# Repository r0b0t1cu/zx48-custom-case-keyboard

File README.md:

# ZX Spectrum 48k custom case, keyboard and keycaps

A custom 3D-printed case, keycap set, and keyboard PCB for the ZX Spectrum 48K.

## Why

This started with a ULA chip I had sitting around doing nothing, and a friend who handed me a [PABB Issue 3B PCB](https://www.pcbway.com/project/shareproject/ZX_Spectrum_48_Issue_3B_Redrawn.html). One thing led to another, and the mainboard needed a case and a keyboard to go with it — so I designed both from scratch, along with a few other addons along the way.

## Compatibility

The case is designed around the classic ZX Spectrum 48K PCB footprint and mounting hole layout. It's compatible with:

- Original ZX Spectrum 48K
- ZX Spectrum 48K+
- Any clone board sharing the same PCB size and mounting hole layout (confirmed working with the **Harlequin 128**)

The case is built to be tall enough to accomodate my mods. For example the [ZX Spectrum 27C512 EPROM Adapter](https://github.com/r0b0t1cu/ZX-Spectrum-27C512-EPROM-Adapter).

## What's included

### Case (`/case`)
A simplified, more angular take on the classic Spectrum enclosure, split into three printed parts: bottom shell, back plate, and top. A separate top variant is included for builds using a Harlequin 128 board.

The back plate is modeled to fit the [ZX-Spectrum-AV-Adapter](https://github.com/r0b0t1cu/ZX-Spectrum-AV-Adapter), not the stock Spectrum TV-out connector.

- `FREECAD/` — native FreeCAD source files
- `STEP/` — STEP exports
- `STL/` — ready-to-slice STL files

### Keycaps (`/keycaps`)
Full Spectrum 48K keycap set (letters, numbers, and CS/SS/SP/CR), modeled individually for two-color printing — each key has a separate body and legend (text) piece. Legends use the [Rubik](https://fonts.google.com/specimen/Rubik) typeface.

- `FREECAD/` — native FreeCAD source files, one per key
- `STEP/` — STEP exports
- `STL/` — one `-Body.stl` and one `-Text.stl` per key, for multi-material/multi-color printing
- `3MF/` — pre-arranged print-ready project files with color separation already set up (a Bambu Lab A1-specific version and a generic version)

### Keyboard PCB (`/keyboard-pcb`)
A custom keyboard PCB for use with Cherry MX (and compatible) switches.

Full KiCad project included, plus a fabrication-ready production folder (BOM, CPL, netlist, Gerbers) for ordering directly from a fab house such as PCBWay or JLCPCB.

---

If you enjoy my projects and would like to support my work, you can do so through PCBWay. You can also order the PCBs for this project directly from the link below. Every bit of support is appreciated!

<p>
  
</p>

---

## 3D Printing

- **Material:** PLA
- **Layer height:** 0.2 mm
- **Infill:** 15%
- **Orientation:** flat side down
- **Supports:** a few small supports needed

## Assembly

Case parts are held together with **M3 screws** — all mounting holes are sized for M3.

## Credits & licenses

- All files in this repository (case, keycaps, keyboard PCB) are released under the **MIT License** — see [LICENSE](LICENSE).
- Keycap legends use the **Rubik** typeface by Google Fonts, licensed under the [SIL Open Font License](https://fonts.google.com/specimen/Rubik).
- This case and keyboard are designed to fit a ZX Spectrum 48K mainboard such as [PABB's Issue 3B redraw](https://www.pcbway.com/project/shareproject/ZX_Spectrum_48_Issue_3B_Redrawn.html), which is a **separate project licensed CC BY-NC-SA** and is *not* included or redistributed here.

## Related projects

- [ZX-Spectrum-AV-Adapter](https://github.com/r0b0t1cu/ZX-Spectrum-AV-Adapter) — custom composite video mod
- [ZX-Spectrum-27C512-EPROM-Adapter](https://github.com/r0b0t1cu/ZX-Spectrum-27C512-EPROM-Adapter) — custom EPROM adapter

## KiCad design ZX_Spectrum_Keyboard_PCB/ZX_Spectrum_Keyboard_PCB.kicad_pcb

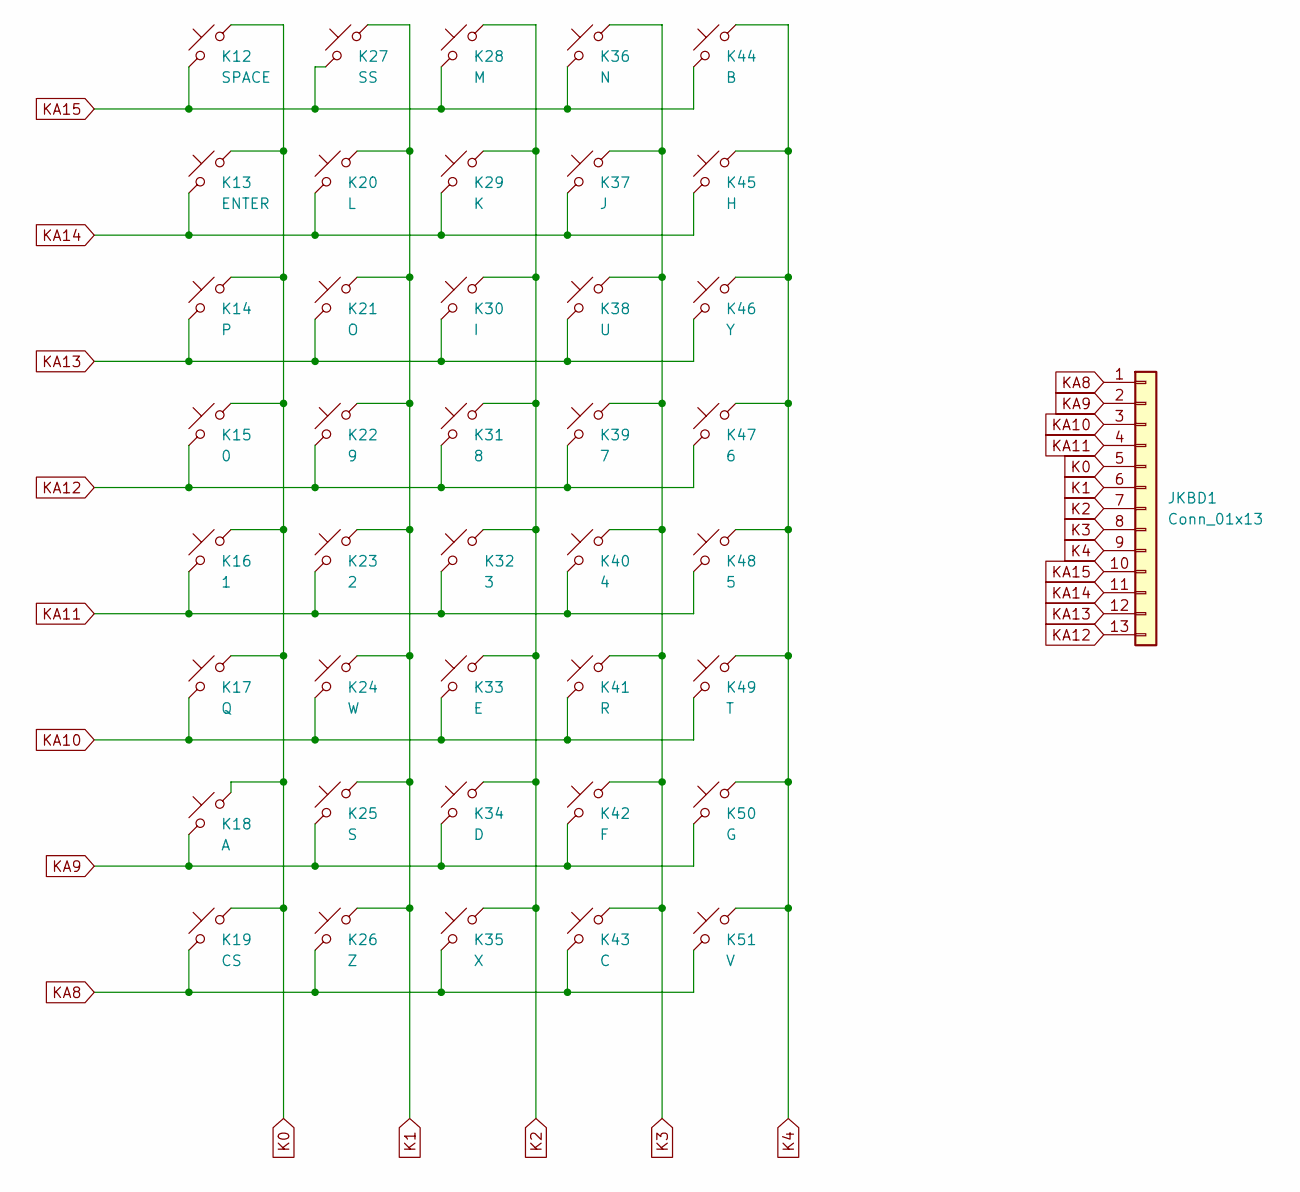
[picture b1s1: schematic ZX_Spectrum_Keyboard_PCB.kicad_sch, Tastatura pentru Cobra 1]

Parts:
JKBD1: Conn_01x13; PinSocket_1x13_P2.54mm_Vertical
K12: SPACE; SW_Cherry_MX_1.00u_PCB
K13: ENTER; SW_Cherry_MX_1.00u_PCB
K14: P; SW_Cherry_MX_1.00u_PCB
K15: 0; SW_Cherry_MX_1.00u_PCB
K16: 1; SW_Cherry_MX_1.00u_PCB
K17: Q; SW_Cherry_MX_1.00u_PCB
K18: A; SW_Cherry_MX_1.00u_PCB
K19: CS; SW_Cherry_MX_1.00u_PCB
K20: L; SW_Cherry_MX_1.00u_PCB
K21: O; SW_Cherry_MX_1.00u_PCB
K22: 9; SW_Cherry_MX_1.00u_PCB
K23: 2; SW_Cherry_MX_1.00u_PCB
K24: W; SW_Cherry_MX_1.00u_PCB
K25: S; SW_Cherry_MX_1.00u_PCB
K26: Z; SW_Cherry_MX_1.00u_PCB
K27: SS; SW_Cherry_MX_1.00u_PCB
K28: M; SW_Cherry_MX_1.00u_PCB
K29: K; SW_Cherry_MX_1.00u_PCB
K30: I; SW_Cherry_MX_1.00u_PCB
K31: 8; SW_Cherry_MX_1.00u_PCB
K32: 3; SW_Cherry_MX_1.00u_PCB
K33: E; SW_Cherry_MX_1.00u_PCB
K34: D; SW_Cherry_MX_1.00u_PCB
K35: X; SW_Cherry_MX_1.00u_PCB
K36: N; SW_Cherry_MX_1.00u_PCB
K37: J; SW_Cherry_MX_1.00u_PCB
K38: U; SW_Cherry_MX_1.00u_PCB
K39: 7; SW_Cherry_MX_1.00u_PCB
K40: 4; SW_Cherry_MX_1.00u_PCB
K41: R; SW_Cherry_MX_1.00u_PCB
K42: F; SW_Cherry_MX_1.00u_PCB
K43: C; SW_Cherry_MX_1.00u_PCB
K44: B; SW_Cherry_MX_1.00u_PCB
K45: H; SW_Cherry_MX_1.00u_PCB
K46: Y; SW_Cherry_MX_1.00u_PCB
K47: 6; SW_Cherry_MX_1.00u_PCB
K48: 5; SW_Cherry_MX_1.00u_PCB
K49: T; SW_Cherry_MX_1.00u_PCB
K50: G; SW_Cherry_MX_1.00u_PCB
K51: V; SW_Cherry_MX_1.00u_PCB

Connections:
K0: JKBD1.5, K12.2, K13.2, K14.2, K15.2, K16.2, K17.2, K18.2, K19.2
K1: JKBD1.6, K20.2, K21.2, K22.2, K23.2, K24.2, K25.2, K26.2, K27.2
K2: JKBD1.7, K28.2, K29.2, K30.2, K31.2, K32.2, K33.2, K34.2, K35.2
K3: JKBD1.8, K36.2, K37.2, K38.2, K39.2, K40.2, K41.2, K42.2, K43.2
K4: JKBD1.9, K44.2, K45.2, K46.2, K47.2, K48.2, K49.2, K50.2, K51.2
KA8: JKBD1.1, K19.1, K26.1, K35.1, K43.1, K51.1
KA9: JKBD1.2, K18.1, K25.1, K34.1, K42.1, K50.1
KA10: JKBD1.3, K17.1, K24.1, K33.1, K41.1, K49.1
KA11: JKBD1.4, K16.1, K23.1, K32.1, K40.1, K48.1
KA12: JKBD1.13, K15.1, K22.1, K31.1, K39.1, K47.1
KA13: JKBD1.12, K14.1, K21.1, K30.1, K38.1, K46.1
KA14: JKBD1.11, K13.1, K20.1, K29.1, K37.1, K45.1
KA15: JKBD1.10, K12.1, K27.1, K28.1, K36.1, K44.1

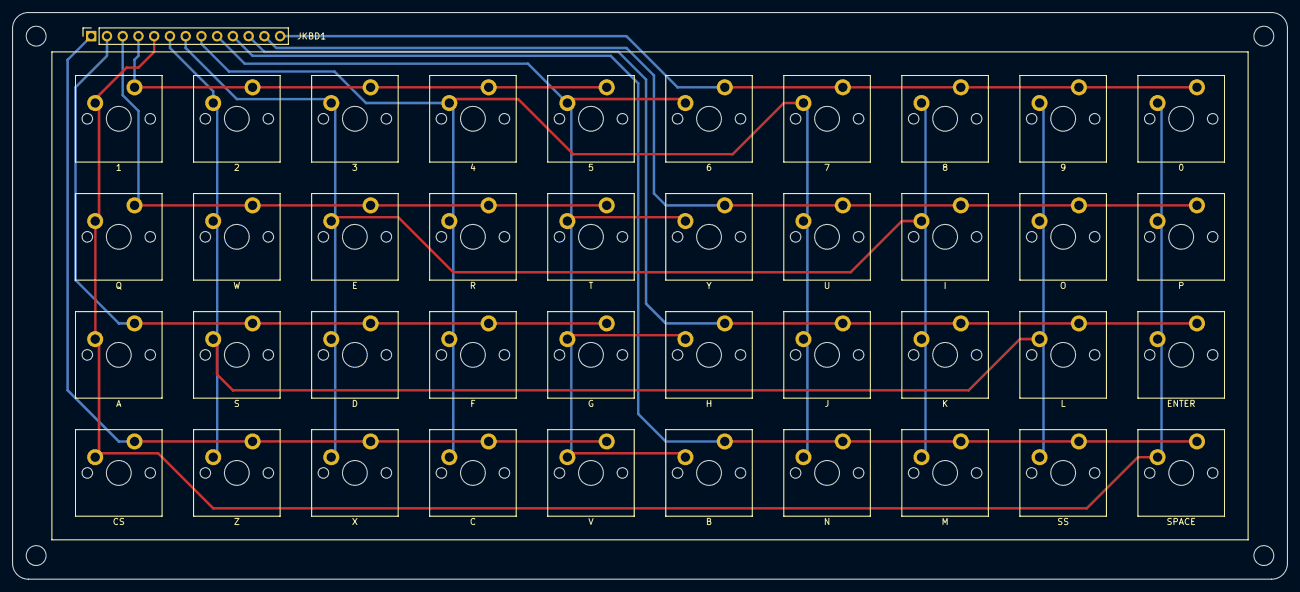
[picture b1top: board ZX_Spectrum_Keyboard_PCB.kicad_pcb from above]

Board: 2 copper layers, 205.7 x 91.4 mm, 45 parts (0 on the bottom side), 13 nets.

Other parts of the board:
M1, M2, M3, M4: MountingHole_3.2mm_M3

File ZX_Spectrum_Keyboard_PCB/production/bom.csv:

Designator,Footprint,Quantity,Value,LCSC Part #
JKBD1,PinSocket_1x13_P2.54mm_Vertical,1,Conn_01x13,
K12,SW_Cherry_MX_1.00u_PCB,1,SPACE,
K13,SW_Cherry_MX_1.00u_PCB,1,ENTER,
K14,SW_Cherry_MX_1.00u_PCB,1,P,
K15,SW_Cherry_MX_1.00u_PCB,1,0,
K16,SW_Cherry_MX_1.00u_PCB,1,1,
K17,SW_Cherry_MX_1.00u_PCB,1,Q,
K18,SW_Cherry_MX_1.00u_PCB,1,A,
K19,SW_Cherry_MX_1.00u_PCB,1,CS,
K20,SW_Cherry_MX_1.00u_PCB,1,L,
K21,SW_Cherry_MX_1.00u_PCB,1,O,
K22,SW_Cherry_MX_1.00u_PCB,1,9,
K23,SW_Cherry_MX_1.00u_PCB,1,2,
K24,SW_Cherry_MX_1.00u_PCB,1,W,
K25,SW_Cherry_MX_1.00u_PCB,1,S,
K26,SW_Cherry_MX_1.00u_PCB,1,Z,
K27,SW_Cherry_MX_1.00u_PCB,1,SS,
K28,SW_Cherry_MX_1.00u_PCB,1,M,
K29,SW_Cherry_MX_1.00u_PCB,1,K,
K30,SW_Cherry_MX_1.00u_PCB,1,I,
K31,SW_Cherry_MX_1.00u_PCB,1,8,
K32,SW_Cherry_MX_1.00u_PCB,1,3,
K33,SW_Cherry_MX_1.00u_PCB,1,E,
K34,SW_Cherry_MX_1.00u_PCB,1,D,
K35,SW_Cherry_MX_1.00u_PCB,1,X,
K36,SW_Cherry_MX_1.00u_PCB,1,N,
K37,SW_Cherry_MX_1.00u_PCB,1,J,
K38,SW_Cherry_MX_1.00u_PCB,1,U,
K39,SW_Cherry_MX_1.00u_PCB,1,7,
K40,SW_Cherry_MX_1.00u_PCB,1,4,
K41,SW_Cherry_MX_1.00u_PCB,1,R,
K42,SW_Cherry_MX_1.00u_PCB,1,F,
K43,SW_Cherry_MX_1.00u_PCB,1,C,
K44,SW_Cherry_MX_1.00u_PCB,1,B,
K45,SW_Cherry_MX_1.00u_PCB,1,H,
K46,SW_Cherry_MX_1.00u_PCB,1,Y,
K47,SW_Cherry_MX_1.00u_PCB,1,6,
K48,SW_Cherry_MX_1.00u_PCB,1,5,
K49,SW_Cherry_MX_1.00u_PCB,1,T,
K50,SW_Cherry_MX_1.00u_PCB,1,G,
K51,SW_Cherry_MX_1.00u_PCB,1,V,
